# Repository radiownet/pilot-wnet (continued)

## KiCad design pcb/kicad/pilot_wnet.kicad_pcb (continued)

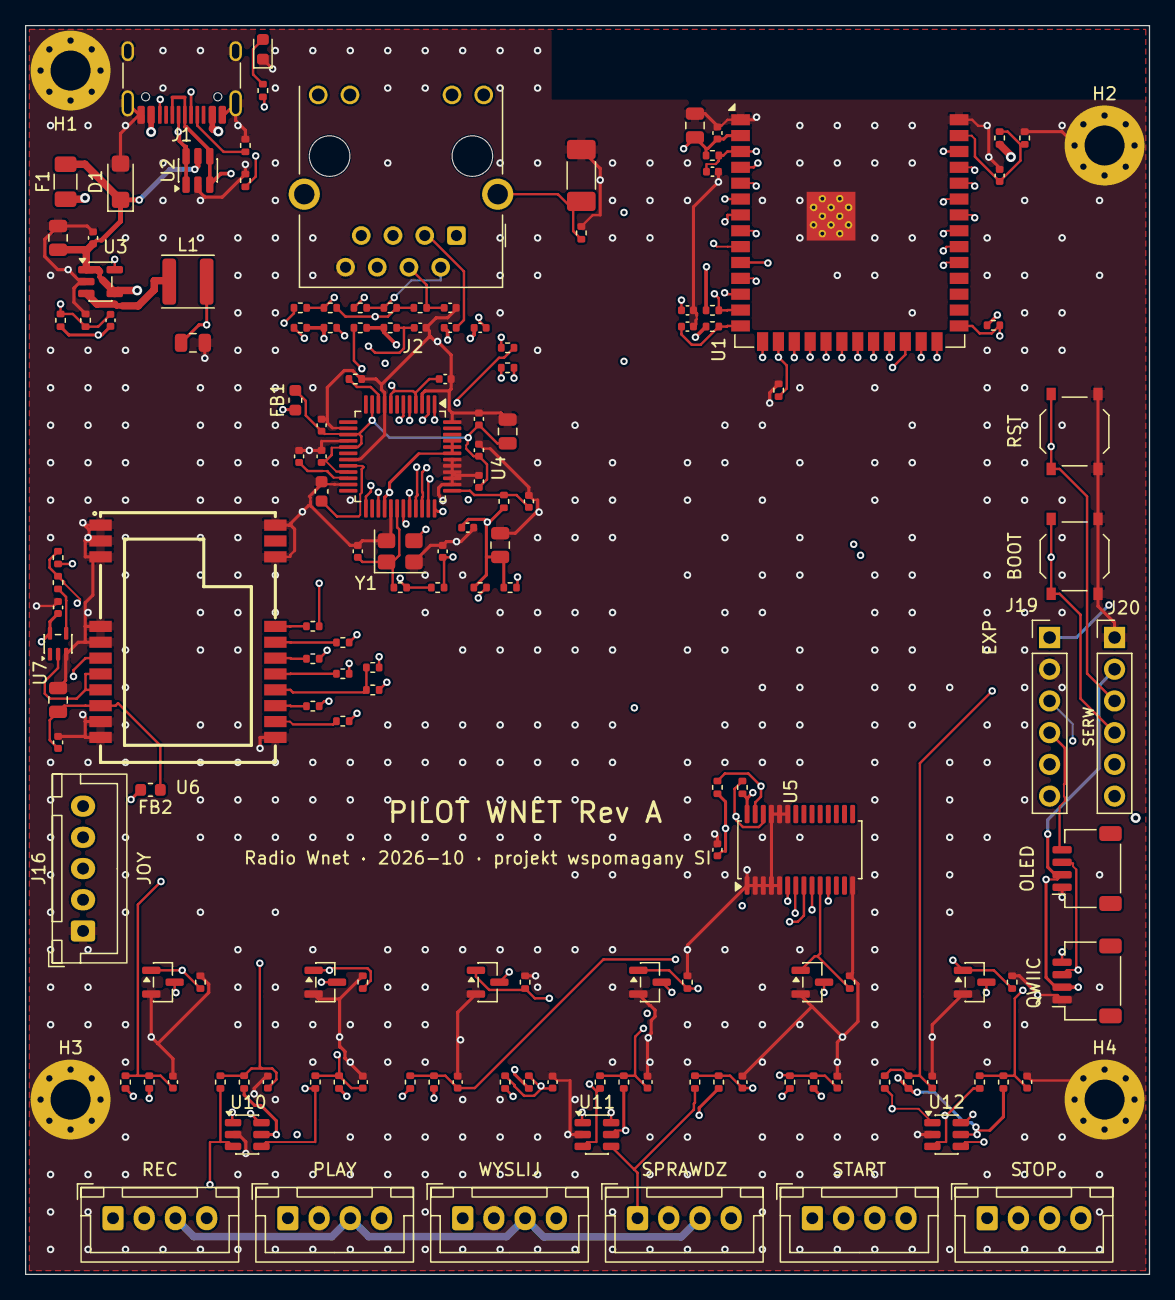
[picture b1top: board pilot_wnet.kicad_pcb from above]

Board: 4 copper layers, 90.0 x 100.0 mm, 153 parts (0 on the bottom side), 103 nets.

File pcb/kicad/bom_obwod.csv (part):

ref,wartosc,footprint,lcsc,dnp,uwaga
C1,10uF 25V,Capacitor_SMD:C_0805_2012Metric,C15850,,
C2,100nF,Capacitor_SMD:C_0402_1005Metric,C1525,,
C3,22uF 25V,Capacitor_SMD:C_0805_2012Metric,C45783,,
C4,6.8pF C0G,Capacitor_SMD:C_0402_1005Metric,C237286,1,feed-forward TLV62569 (opcja)
C5,22uF 25V,Capacitor_SMD:C_0805_2012Metric,C45783,,
C6,100nF,Capacitor_SMD:C_0402_1005Metric,C1525,,
C7,1uF,Capacitor_SMD:C_0402_1005Metric,C52923,,
C8,18pF C0G,Capacitor_SMD:C_0402_1005Metric,C1549,1,
C9,18pF C0G,Capacitor_SMD:C_0402_1005Metric,C1549,1,
C10,10nF,Capacitor_SMD:C_0402_1005Metric,C15195,,
C11,10nF,Capacitor_SMD:C_0402_1005Metric,C15195,,
C12,10nF,Capacitor_SMD:C_0402_1005Metric,C15195,,
C13,10nF,Capacitor_SMD:C_0402_1005Metric,C15195,,
C14,10nF,Capacitor_SMD:C_0402_1005Metric,C15195,,
C15,10nF,Capacitor_SMD:C_0402_1005Metric,C15195,,
C16,10nF,Capacitor_SMD:C_0402_1005Metric,C15195,,
C17,10nF,Capacitor_SMD:C_0402_1005Metric,C15195,,
C18,10nF,Capacitor_SMD:C_0402_1005Metric,C15195,,
C19,10nF,Capacitor_SMD:C_0402_1005Metric,C15195,,
C20,100nF,Capacitor_SMD:C_0402_1005Metric,C1525,1,
C21,100nF,Capacitor_SMD:C_0402_1005Metric,C1525,,
C30,100nF,Capacitor_SMD:C_0402_1005Metric,C1525,,
C31,100nF,Capacitor_SMD:C_0402_1005Metric,C1525,,
C32,100nF,Capacitor_SMD:C_0402_1005Metric,C1525,,
C33,100nF,Capacitor_SMD:C_0402_1005Metric,C1525,,
C34,100nF,Capacitor_SMD:C_0402_1005Metric,C1525,,
C35,100nF,Capacitor_SMD:C_0402_1005Metric,C1525,,
C36,10uF 25V,Capacitor_SMD:C_0805_2012Metric,C15850,,
C37,10nF,Capacitor_SMD:C_0402_1005Metric,C15195,,
C38,4.7uF,Capacitor_SMD:C_0603_1608Metric,C19666,,TOCAP W5500
C39,1uF,Capacitor_SMD:C_0402_1005Metric,C52923,,
C40,18pF C0G,Capacitor_SMD:C_0402_1005Metric,C1549,,
C41,18pF C0G,Capacitor_SMD:C_0402_1005Metric,C1549,,
C42,22nF,Capacitor_SMD:C_0402_1005Metric,C1532,,TCT Ethernet
C43,10nF,Capacitor_SMD:C_0402_1005Metric,C15195,,
C44,100nF,Capacitor_SMD:C_0402_1005Metric,C1525,,
C45,10uF 25V,Capacitor_SMD:C_0805_2012Metric,C15850,,
C46,6.8nF,Capacitor_SMD:C_0402_1005Metric,C318580,,sprzężenie RX Ethernet
C47,6.8nF,Capacitor_SMD:C_0402_1005Metric,C318580,,sprzężenie RX Ethernet
C48,1nF 2kV,Capacitor_SMD:C_1808_4520Metric,C76916,,ekran RJ45 -> GND
C50,10uF 25V,Capacitor_SMD:C_0805_2012Metric,C15850,,
C51,100nF,Capacitor_SMD:C_0402_1005Metric,C1525,,
C52,100nF,Capacitor_SMD:C_0402_1005Metric,C1525,,
D1,SMF5.0A,Diode_SMD:D_SMF,C151296,,jednokierunkowy
D2,zielona,LED_SMD:LED_0603_1608Metric,C12065,,
F1,1.1A hold,Fuse:Fuse_1206_3216Metric,C126818,,"Littelfuse 1206L110THYR: 1,1 A hold, 2,2 A trip, 8 V (LCSC 19.11; było C70069 = 250 mA)"
FB1,600R@100MHz 1.3A,Inductor_SMD:L_0603_1608Metric,C85833,,"Murata BLM18KG601SN1D, 3V3 -> 3V3A"
FB2,600R@100MHz 1.3A,Inductor_SMD:L_0603_1608Metric,C85833,,"Murata BLM18KG601SN1D, 3V3 -> 3V3A"
J1,TYPE-C-31-M-12,pilot_jlc:USB_C_Receptacle_HRO_TYPE-C-31-M-12_Pilot,C165948,,
J2,HR911105A,Connector_RJ:RJ45_Hanrun_HR911105A_Horizontal,C12074,,THT
J10,B4B-XH-A,Connector_JST:JST_XH_B4B-XH-A_1x04_P2.50mm_Vertical,C144395,,THT
J11,B4B-XH-A,Connector_JST:JST_XH_B4B-XH-A_1x04_P2.50mm_Vertical,C144395,,THT
J12,B4B-XH-A,Connector_JST:JST_XH_B4B-XH-A_1x04_P2.50mm_Vertical,C144395,,THT
J13,B4B-XH-A,Connector_JST:JST_XH_B4B-XH-A_1x04_P2.50mm_Vertical,C144395,,THT
J14,B4B-XH-A,Connector_JST:JST_XH_B4B-XH-A_1x04_P2.50mm_Vertical,C144395,,THT
J15,B4B-XH-A,Connector_JST:JST_XH_B4B-XH-A_1x04_P2.50mm_Vertical,C144395,,THT
J16,B5B-XH-A,Connector_JST:JST_XH_B5B-XH-A_1x05_P2.50mm_Vertical,C157991,,THT
J17,SM04B-SRSS-TB,Connector_JST:JST_SH_SM04B-SRSS-TB_1x04-1MP_P1.00mm_Horizontal,C160404,,Qwiic
J18,SM04B-SRSS-TB,Connector_JST:JST_SH_SM04B-SRSS-TB_1x04-1MP_P1.00mm_Horizontal,C160404,,Qwiic
J19,1x6 2.54,Connector_PinHeader_2.54mm:PinHeader_1x06_P2.54mm_Vertical,C37208,,THT
J20,1x6 2.54,Connector_PinHeader_2.54mm:PinHeader_1x06_P2.54mm_Vertical,C37208,,THT
L1,2.2uH,Inductor_SMD:L_Changjiang_FNR4030S,C167869,,"FNR4030S2R2MT: Isat 5,8 A (LCSC 19.11; było C167219 = 3,3 uH 7x6,6 mm)"
Q1,AO3400A,Package_TO_SOT_SMD:SOT-23,C20917,1,
Q2,AO3400A,Package_TO_SOT_SMD:SOT-23,C20917,1,
Q3,AO3400A,Package_TO_SOT_SMD:SOT-23,C20917,1,
Q4,AO3400A,Package_TO_SOT_SMD:SOT-23,C20917,1,
Q5,AO3400A,Package_TO_SOT_SMD:SOT-23,C20917,1,
Q6,AO3400A,Package_TO_SOT_SMD:SOT-23,C20917,1,
R1,5.1k,Resistor_SMD:R_0402_1005Metric,C25905,,
R2,5.1k,Resistor_SMD:R_0402_1005Metric,C25905,,
R3,100k,Resistor_SMD:R_0402_1005Metric,C25741,,
R4,22k 1%,Resistor_SMD:R_0402_1005Metric,C25768,,"dzielnik FB: 0,6 × (1 + 100/22) = 3,327 V"
R5,10k,Resistor_SMD:R_0402_1005Metric,C25744,,
R6,22,Resistor_SMD:R_0402_1005Metric,C25092,,szeregowe USB przy module (HDG Espressif)
R7,22,Resistor_SMD:R_0402_1005Metric,C25092,,szeregowe USB przy module (HDG Espressif)
R9,10k,Resistor_SMD:R_0402_1005Metric,C25744,,
R10,1k,Resistor_SMD:R_0402_1005Metric,C11702,,
R11,1k,Resistor_SMD:R_0402_1005Metric,C11702,,
R12,1k,Resistor_SMD:R_0402_1005Metric,C11702,,
R13,1k,Resistor_SMD:R_0402_1005Metric,C11702,,
R14,1k,Resistor_SMD:R_0402_1005Metric,C11702,,
R15,1k,Resistor_SMD:R_0402_1005Metric,C11702,,
R16,1k,Resistor_SMD:R_0402_1005Metric,C11702,,
R17,1k,Resistor_SMD:R_0402_1005Metric,C11702,,
R18,1k,Resistor_SMD:R_0402_1005Metric,C11702,,
R19,1k,Resistor_SMD:R_0402_1005Metric,C11702,,
R20,10k,Resistor_SMD:R_0402_1005Metric,C25744,,
R21,10k,Resistor_SMD:R_0402_1005Metric,C25744,,
R22,10k,Resistor_SMD:R_0402_1005Metric,C25744,,
R23,10k,Resistor_SMD:R_0402_1005Metric,C25744,,
R24,10k,Resistor_SMD:R_0402_1005Metric,C25744,,
R25,10k,Resistor_SMD:R_0402_1005Metric,C25744,,
R26,10k,Resistor_SMD:R_0402_1005Metric,C25744,,
R27,10k,Resistor_SMD:R_0402_1005Metric,C25744,,
R28,10k,Resistor_SMD:R_0402_1005Metric,C25744,,
R29,10k,Resistor_SMD:R_0402_1005Metric,C25744,,
R30,4.7k,Resistor_SMD:R_0402_1005Metric,C25900,,
R31,4.7k,Resistor_SMD:R_0402_1005Metric,C25900,,
R40,100k,Resistor_SMD:R_0402_1005Metric,C25741,1,
R41,100k,Resistor_SMD:R_0402_1005Metric,C25741,1,
R42,100k,Resistor_SMD:R_0402_1005Metric,C25741,1,
R43,100k,Resistor_SMD:R_0402_1005Metric,C25741,1,
R44,100k,Resistor_SMD:R_0402_1005Metric,C25741,1,
R45,100k,Resistor_SMD:R_0402_1005Metric,C25741,1,
R50,1k,Resistor_SMD:R_0402_1005Metric,C11702,,
R51,100k,Resistor_SMD:R_0402_1005Metric,C25741,,
R52,100k,Resistor_SMD:R_0402_1005Metric,C25741,,
R53,49.9 1%,Resistor_SMD:R_0402_1005Metric,C25120,,
R54,49.9 1%,Resistor_SMD:R_0402_1005Metric,C25120,,
R55,0,Resistor_SMD:R_0402_1005Metric,C17168,,
R56,0,Resistor_SMD:R_0402_1005Metric,C17168,,
R57,10 1%,Resistor_SMD:R_0402_1005Metric,C25077,,TCT gniazda RJ45 (referencja WIZnet)
R58,0,Resistor_SMD:R_0402_1005Metric,C17168,,
R59,1M,Resistor_SMD:R_0402_1005Metric,C26083,,równolegle do kwarcu W5500
R60,12.4k 1%,Resistor_SMD:R_0402_1005Metric,C11692,,EXRES1 W5500
R61,10k,Resistor_SMD:R_0402_1005Metric,C25744,,
R62,0,Resistor_SMD:R_0402_1005Metric,C17168,,
R63,0,Resistor_SMD:R_0402_1005Metric,C17168,,
R64,49.9 1%,Resistor_SMD:R_0402_1005Metric,C25120,,
R65,49.9 1%,Resistor_SMD:R_0402_1005Metric,C25120,,
R66,330,Resistor_SMD:R_0402_1005Metric,C25104,,
R67,330,Resistor_SMD:R_0402_1005Metric,C25104,,
R68,4.7k,Resistor_SMD:R_0402_1005Metric,C25900,,
R69,4.7k,Resistor_SMD:R_0402_1005Metric,C25900,,
R70,200,Resistor_SMD:R_0402_1005Metric,C25087,,
R71,200,Resistor_SMD:R_0402_1005Metric,C25087,,
R72,200,Resistor_SMD:R_0402_1005Metric,C25087,,
R73,200,Resistor_SMD:R_0402_1005Metric,C25087,,
R74,200,Resistor_SMD:R_0402_1005Metric,C25087,,
R75,200,Resistor_SMD:R_0402_1005Metric,C25087,,
R76,0,Resistor_SMD:R_0402_1005Metric,C17168,,
R77,0,Resistor_SMD:R_0402_1005Metric,C17168,1,
R78,10k,Resistor_SMD:R_0402_1005Metric,C25744,,
R79,0,Resistor_SMD:R_0402_1005Metric,C17168,,
R80,0,Resistor_SMD:R_0402_1005Metric,C17168,1,
R82,0,Resistor_SMD:R_0402_1005Metric,C17168,1,
SW1,TS-1187A-B-A-B,Button_Switch_SMD:SW_Push_1P1T_XKB_TS-1187A,C318884,,
SW2,TS-1187A-B-A-B,Button_Switch_SMD:SW_Push_1P1T_XKB_TS-1187A,C318884,,
U1,ESP32-S3-WROOM-1-N16R8,pilot_jlc:ESP32-S3-WROOM-1_Pilot,C2913202,,antena PCB przy tylnej krawędzi (DECYZJE D3)
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
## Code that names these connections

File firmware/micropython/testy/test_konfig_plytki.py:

# -*- coding: utf-8 -*-
"""Testy tabeli pinów Rev A (CPython): zgodność z pcb/obwod.py i wykrywanie konfliktów."""
import os
import re
import sys
import unittest

TU = os.path.dirname(os.path.abspath(__file__))
sys.path.insert(0, os.path.join(TU, "..", "lib"))
import konfig_plytki as K  # noqa: E402
import pilot_wejscia as W  # noqa: E402

OBWOD = os.path.join(TU, "..", "..", "..", "pcb", "obwod.py")


def _obwod():
    with open(OBWOD, encoding="utf-8") as f:
        return f.read()


def _gpio(wzor_przed, t=None):
    """Numer GPIO z `<wzor_przed>io(N)` — także w opakowaniu `nazwij(io(N), "...")`."""
    t = _obwod() if t is None else t
    m = re.search(wzor_przed + r"\s*(?:nazwij\()?io\((\d+)\)", t)
    return int(m.group(1)) if m else None


class TestZgodnoscZObwodem(unittest.TestCase):
    """Piny przepisane z obwod.py — test czyta plik SKiDL jako tekst, bez importu SKiDL."""

    def test_wejscia(self):
        blok = re.search(r"WEJSCIA = \[(.*?)\]", _obwod(), re.S).group(1)
        z_obwodu = {n: int(g) for n, g in re.findall(r'\("(\w+)", (\d+)\)', blok)}
        self.assertEqual(z_obwodu, dict(K.WEJSCIA))

    def test_ethernet(self):
        blok = re.search(r"eth = \{(.*?)\}\n", _obwod(), re.S).group(1)
        z_obwodu = {s: int(g) for s, g in re.findall(r'\("(ETH_\w+)", (\d+)\)', blok)}
        self.assertEqual(z_obwodu, {"ETH_CS": K.ETH_CS, "ETH_SCLK": K.ETH_SCLK, "ETH_MISO": K.ETH_MISO,
                                    "ETH_MOSI": K.ETH_MOSI, "ETH_INT": K.ETH_INT})

    def test_lora(self):
        t = _obwod()
        blok = re.search(r"lora = \[(.*?)\]\n", t, re.S).group(1)
        z_obwodu = {s: int(g) for s, g in re.findall(r'"(LORA_\w+)", (\d+)\)', blok)}
        self.assertEqual(z_obwodu, {"LORA_NSS": K.LORA_NSS, "LORA_SCK": K.LORA_SCK, "LORA_MOSI": K.LORA_MOSI,
                                    "LORA_MISO": K.LORA_MISO, "LORA_BUSY": K.LORA_BUSY, "LORA_DIO1": K.LORA_DIO1})
        self.assertEqual(_gpio(r'"R76", nrst,', t), K.LORA_NRST)

    def test_pozostale(self):
        t = _obwod()
        self.assertEqual(_gpio(r"\bled \+=", t), K.LED_STATUS)
        self.assertEqual(_gpio(r"\bvs \+=", t), K.VSYS_SENSE)
        self.assertEqual(_gpio(r"\bexp13 \+=", t), K.EXP_IO13)
        self.assertEqual(_gpio(r"\bsda \+=", t), K.I2C_SDA)
        self.assertEqual(_gpio(r"\bscl \+=", t), K.I2C_SCL)
        self.assertEqual(_gpio(r"sw_boot\[1\] \+=", t), K.BOOT)
        self.assertIn('"PCA9685PW", "PCA", "U5", dnp=True', t)   # PCA9685 niemontowany
        self.assertIn("ETH_RST", t)                              # reset W5500 tylko siecią RC


class TestTabela(unittest.TestCase):
    def test_brak_konfliktow_w_rev_a(self):
        self.assertEqual(K.sprawdz(), [])

    def test_kolejnosc_bitow_maski(self):
        nazwy = [n for n, _ in K.WEJSCIA]
        self.assertEqual(nazwy.index("REC"), W.R.bit_length() - 1)
        self.assertEqual(nazwy.index("SPRAWDZ"), W.G.bit_length() - 1)
        self.assertEqual(nazwy.index("START"), W.START.bit_length() - 1)
        self.assertEqual(nazwy.index("JOY_RIGHT"), W.PRAWO.bit_length() - 1)
        self.assertEqual(len(K.PINY_MASKI), 10)

    def test_start_nie_na_gpio0(self):
        self.assertNotIn(0, K.PINY_MASKI)   # DECYZJE D9

    def test_psram_wykryty(self):
        for g in (33, 34, 35, 36, 37):
            m = K.piny()
            m["LORA_DIO2_SX1280"] = g
            self.assertTrue(any("PSRAM" in b for b in K.sprawdz(m)), g)

    def test_powtorzenie_wykryte(self):
        m = K.piny()
        m["BTN_PLAY"] = K.ETH_CS
        self.assertTrue(any("dwa razy" in b for b in K.sprawdz(m)))

    def test_niewyprowadzony_wykryty(self):
        m = K.piny()
        m["X"] = 22
        self.assertTrue(any("nie jest wyprowadzony" in b for b in K.sprawdz(m)))

    def test_tcxo(self):
        self.assertTrue(K.sprawdz(tcxo_mv=1500))
        self.assertTrue(K.sprawdz(tcxo_mv=3400))
        self.assertEqual(K.sprawdz(tcxo_mv=2200), [])
        self.assertEqual(K.ostrzezenia(tcxo_mv=1800), [])
        self.assertTrue(K.ostrzezenia(tcxo_mv=2000))

    def test_strapping_jako_ostrzezenie(self):
        m = K.piny()
        m["BTN_REC"] = 46
        self.assertTrue(any("GPIO46" in w for w in K.ostrzezenia(m)))
        self.assertEqual(K.ostrzezenia(), [])


if __name__ == "__main__":
    unittest.main(verbosity=1)

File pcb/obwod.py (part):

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        u4[pin] += n
        n += io(g)
        en_eth[siec] = n
    f.R("R4K7", "R68", V3, en_eth["ETH_CS"])      # CS w stanie wysokim przy resecie (GPIO45 ma słabe ściąganie)
    f.R("R4K7", "R69", V3, en_eth["ETH_INT"])
    v3a = Net("+3V3A")
    v3a.drive = POWER
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    f.C("C6N8", "C47", rx_n, rd_n)
    j2["RD+"] += rd_p
    j2["RD-"] += rd_n
    # masa gniazda: pin 8 (CHS GND) do masy płytki; ekran na wyspę CH_GND, 1 nF / 2 kV do masy, 0 Ω DNP do testów EMC
    j2[8] += GND
    chgnd = Net("CH_GND")
    j2["SH"] += chgnd
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        b += io(g)
    nrst = Net("LORA_NRST")
    u6["NRST"] += nrst
    f.R("R0", "R76", nrst, nazwij(io(2), "LORA_NRST_M"))   # Rev A: NRESET na GPIO2 (R3 §6.4)
    io46 = nazwij(io(46), "ESP_IO46")
    f.R("R0", "R77", nrst, io46, dnp=True)          # zgodność binarna z T-ETH-Elite (GPIO46)
    f.R("R10K", "R78", io46, GND)                   # GPIO46 = 0 przy rozruchu
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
